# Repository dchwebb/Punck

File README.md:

# Punck

Overview
--------

- Audio Demo with Kick, snare and hi hats: [Punck.wav](https://raw.githubusercontent.com/dchwebb/Punck/master/Drum_Sequences/Punck.wav)
- Audio Demo with all voices and samples: [Punck2.wav](https://raw.githubusercontent.com/dchwebb/Punck/master/Drum_Sequences/Punck2.wav)

Punck is drum machine designed for use with Eurorack modular synthesizers. Its five primary voices are Kick, Snare, High Hat and two sample playback channels. In addition Toms and Claps voices are available via MIDI.

It features a built-in drum sequencer with five patterns each with up to 4 bars in length and either 16 or 24 beats per bar.

Voices can be triggered via front panel illuminated buttons, gate input, USB MIDI, serial MIDI and the drum sequencer. All trigger modes are available simultaneously.

Samples are stored on 32MB of internal Flash memory. This storage space is made available as a standard USB drive, requiring no external drives or SD cards.

A browser-based editor allows drum sequences to be entered graphically and detailed parameters of internal voices to be edited. A MIDI mapping facility provides access to different articulations of voices and different samples for the sampler tracks.

Audio DSP
---------

### Kick
The kick drum is modelled on a Roland TR-808 kick. This is generated in five phases, the first three providing an initial steep ramp and discontinuity for the 'click', a fast sine wave at 130Hz and then a slowly decelerating sine wave starting at 60Hz. A potentiometer-controlled 2-pole low pass filter softens the attack and a decay control adjusts the rate at which the level is reduced.

### Snare
The snare is formed of 3 pitched sine wave partials representing the body of the drum and a noise component representing the snare. The partials form the first three modes of vibration of the body. The initial frequency is potentiometer-controlled and the next two partials pitched at multiples of 1.588 and 1.833. The noise component is derived from two random number readings (left and right) and has a decay rate separate from the overall volume envelope. A potentiometer-controlled 2-pole low pass filter attenuates the high frequencies.

### Hi hat
The hi hat consists of 6 square waves with varying rates and levels of frequency modulation. In addition a stereo noise component is used at the beginning of the note. Separate 2-pole high and low pass filters use different ramp envelopes to increase the frequency of the HP filter and reduce the frequency of the LP filter as the note sustains. The decay of the noise and FM partials are separately configurable. When a range of MIDI notes is used to control the hi hat each note will result in a successively more 'open' hi hat sound.

### Sampler A and B
Two independent sample playback voices are provided. These play wave files (8, 16, 24 or 32 bit) stored in the internal flash storage. Each sampler can only play a single sample at a time allowing a maximum of two simultaneously playing voices. Each sampler has a speed control allowing a playback range of 0.5 - 1.5 original speed. Base playback speed is normalised to 48kHz from the original sample rate.

The sample's file name determines the bank (A or B) and index of the sample. Optionally adding suffix '.vNN' to the sample name will set the initial volume of the sample where NN is a value from 0 - 200% and 100% is the original sample level. Eg naming a sample 'B3crash.v150.wav' will make it the 3rd sample on bank B and will play at 150% of its original level.

### Toms
The Toms voice has no UI but is accessible from MIDI and the internal sequencer. An initial fast ramp is followed by a decelerating sine wave. Allocating multiple MIDI notes to playback will allow a range of pitches to be mapped over the MIDI notes.

### Claps
The Claps have no UI but are accessible from MIDI and the internal sequencer. Four 'claps' are played at slightly varying intervals with a sustained phase at the end of the fourth. Each clap is formed of band-pass filtered noise with a center frequency of 1250Hz and a Q of 3.

### Reverb
The reverb engine is derived from Geraint Luff's design: [Signalsmith Audio](https://signalsmith-audio.co.uk/writing/2021/lets-write-a-reverb/). This divides the stereo dry audio into 8 channels which then pass through various diffusion stages followed by a feedback mixer. The diffusion stages use short delay lines and a Hadamard mixing matrix to create a short diffused reverb. The feedback mixer uses longer delays to spread the diffusion channels. The 8 reverb channels are then mixed down to stereo and blended with the dry signal. A 2-pole Low pass filter is used at the input to control high end.

Architecture
------------

### Microcontroller

An STM32H743 microcontroller is responsible for voice generation, USB and MIDI handling, interfacing with the Flash storage devices via QSPI and true random number generation used to generate white noise for various voices. Code is written in C++ 20 using the STM32CubeIDE Eclipse-based IDE. All hardware interfacing is carried out through custom code (ie no STM HAL libraries).

Two internal ADCs read the various potentiometers using DMA circular mode. Timers in PWM mode are used to variably illuminate the LEDs integrated into the push buttons.

An external crystal clocked at 12MHz is scaled using the internal PLL to a main system clock of 400MHz. USB is clocked from the internal 48 MHz RC oscillator.

The microcontroller operates in device mode simultaneously managing three USB classes:

- Mass Storage Class:
Used to provide access to the internal sample flash memory so the storage can be accessed as a normal USB Flash drive. The storage is formatted using FAT16 file system.

- MIDI/Audio Class: 
Bi-directional MIDI is supported to enable playback of drum voices from a USB host. A sysex implementation allows the Browser editor to exchange configuration and playback information with the module.

- Communication Device Class:
A console application is provided to manage and debug the module. This provides information general maintenance tools, configuration options and tools for managing the internal flash storage (formatting, directory listings, disk analysis etc).

### Flash Storage
32MB of internal Flash memory is provided to allow internal sample storage. This consists of two 128Mbit Winbond W25Q128JVS chips connected via QSPI. The MCU operates the flash storage in Dual-flash mode, where 8 bits can be sent/received simultaneously by accessing two Flash memories in parallel. The memory is clocked at ~28MHz.

### Audio DAC
Punck uses a TI PCM5100APW Audio DAC clocked at 48kHz in stereo. The MCU interfaces with the DAC via I2S.

### Audio and Input Conditioning
The stereo audio signal is amplified with a gain of -2.74 using a TL074 op-amp. This also amplifies the tempo clock out signal to around a 5V level. Input clamping is done with MMBT3904 transistors.

### Power Supplies

The Eurorack +/-12V rails have reverse polarity protection and filtering and are then scaled to separate digital and analog 3.3V rails. The 3.3V MCU and DAC digital power supplies are provided by a TI TPS561201 switched-mode synchronous step-down power supply. An LD1117-3.3 linear regulator supplies the analog 3.3V power. A common digital/analog ground plane is used.

- +12V Current Draw: 123mA
- -12V Current Draw: 8mA

Construction
------------

The module is constructed using a sandwich of three PCBs. Schematic and PCB layout carried out in Kicad v6.08.

The component board is a four layer PCB with top mounted components, two inner ground layers and mainly power routing on the bottom layer. 

The control board is a two layer board on which are mounted the jacks, potentiometers, buttons and USB. 

The front panel is a two layer black PCB with exposed coated copper labels and marking.

The prototype was hand-soldered in sections to test each part of the hardware in isolation. This picture shows the power supplies (right), microcontroller (center) and two flash chips (above and to the left of the MCU). The audio DAC and op-amp will be placed on the left hand side:

Web Editor
----------

A Chrome-based web editor allows editing of the 5 internal drum sequences:

Each sequence can be up to 4 bars long with either 16 or 24 steps per bar. The level of each hit can be set and voice specific settings applied (eg choosing sample, snare sustain, hi-hat open/closed amount, tom pitch). Drum sequences can be exported and imported as json files.
Playback start/stop and sequence selection can be controlled from the editor.

Internal drum voice and reverb settings can also be edited:

Prototype
---------

Development was done on an STM Nucleo development board with external surface mount ICs (flash, DAC) soldered to breakout boards for prototyping:

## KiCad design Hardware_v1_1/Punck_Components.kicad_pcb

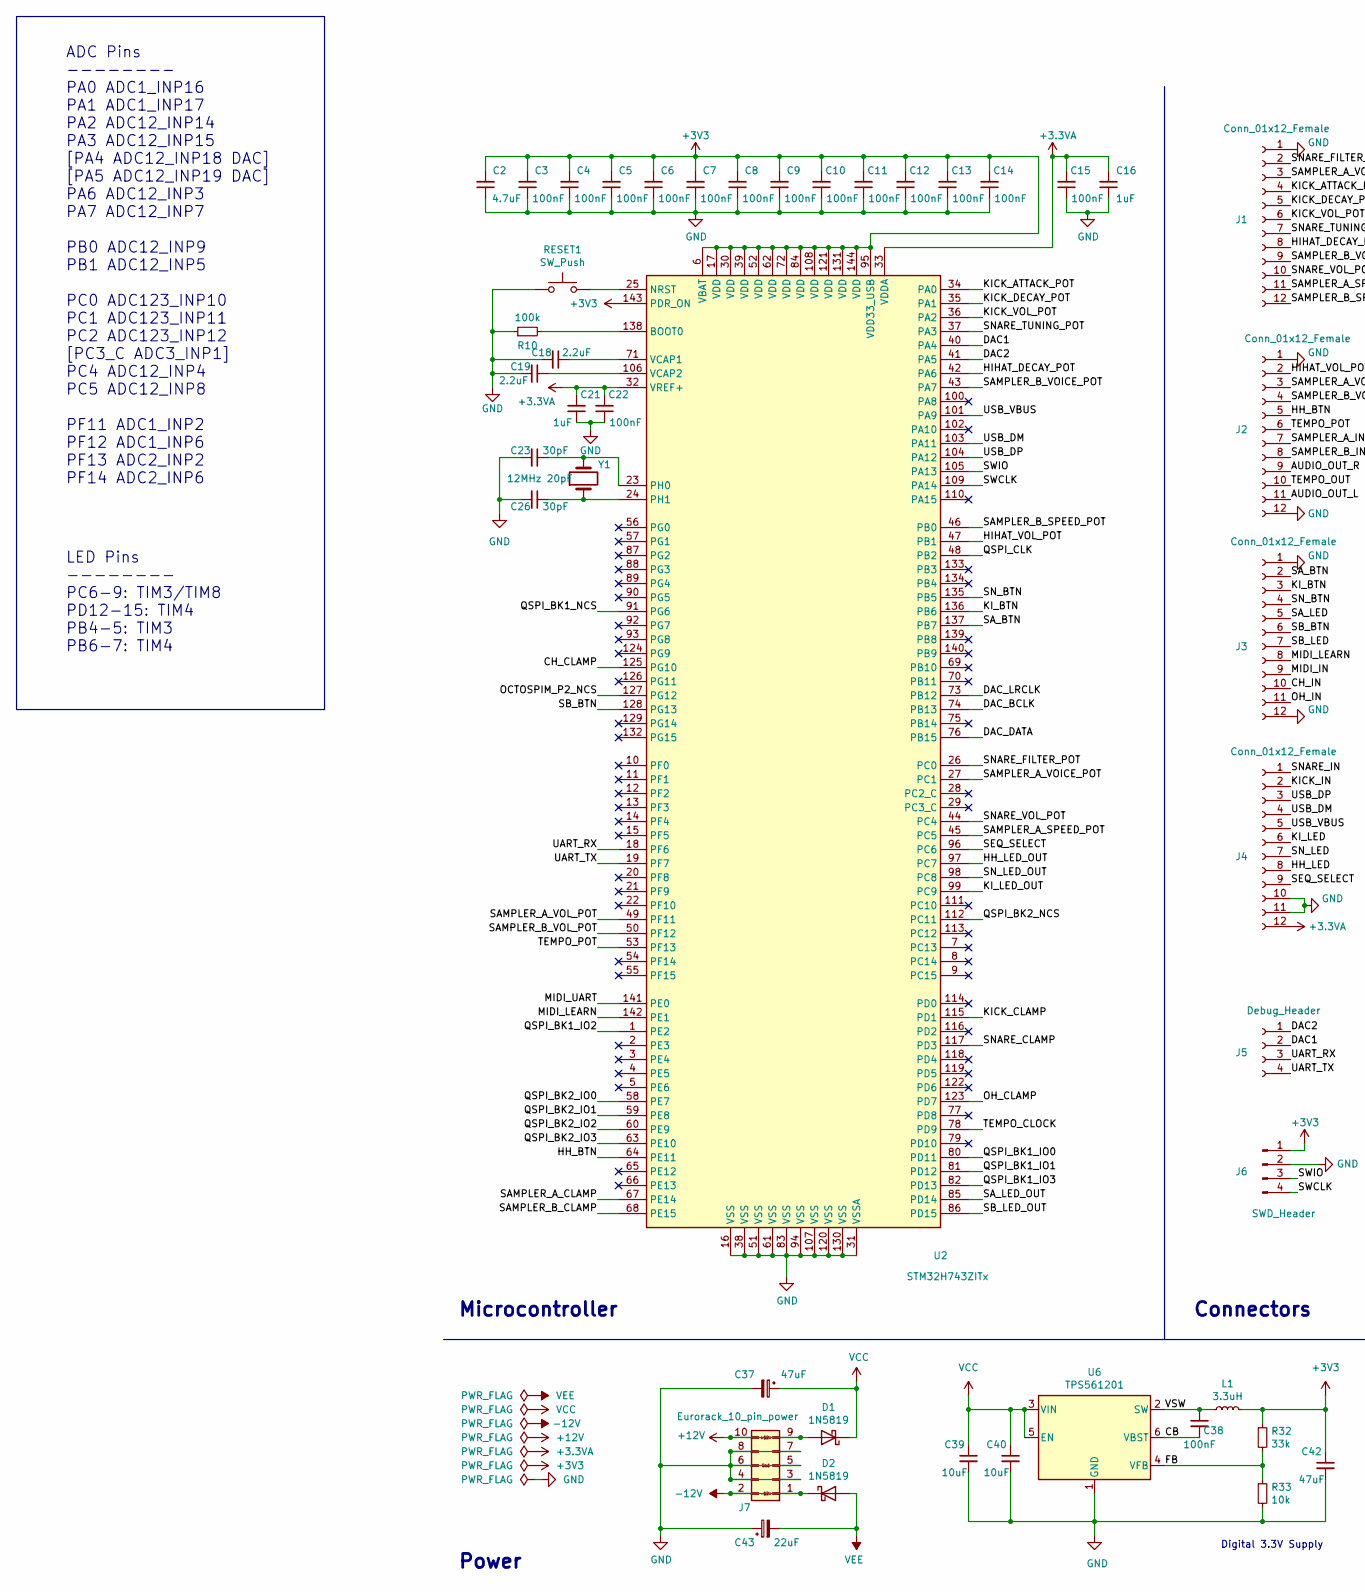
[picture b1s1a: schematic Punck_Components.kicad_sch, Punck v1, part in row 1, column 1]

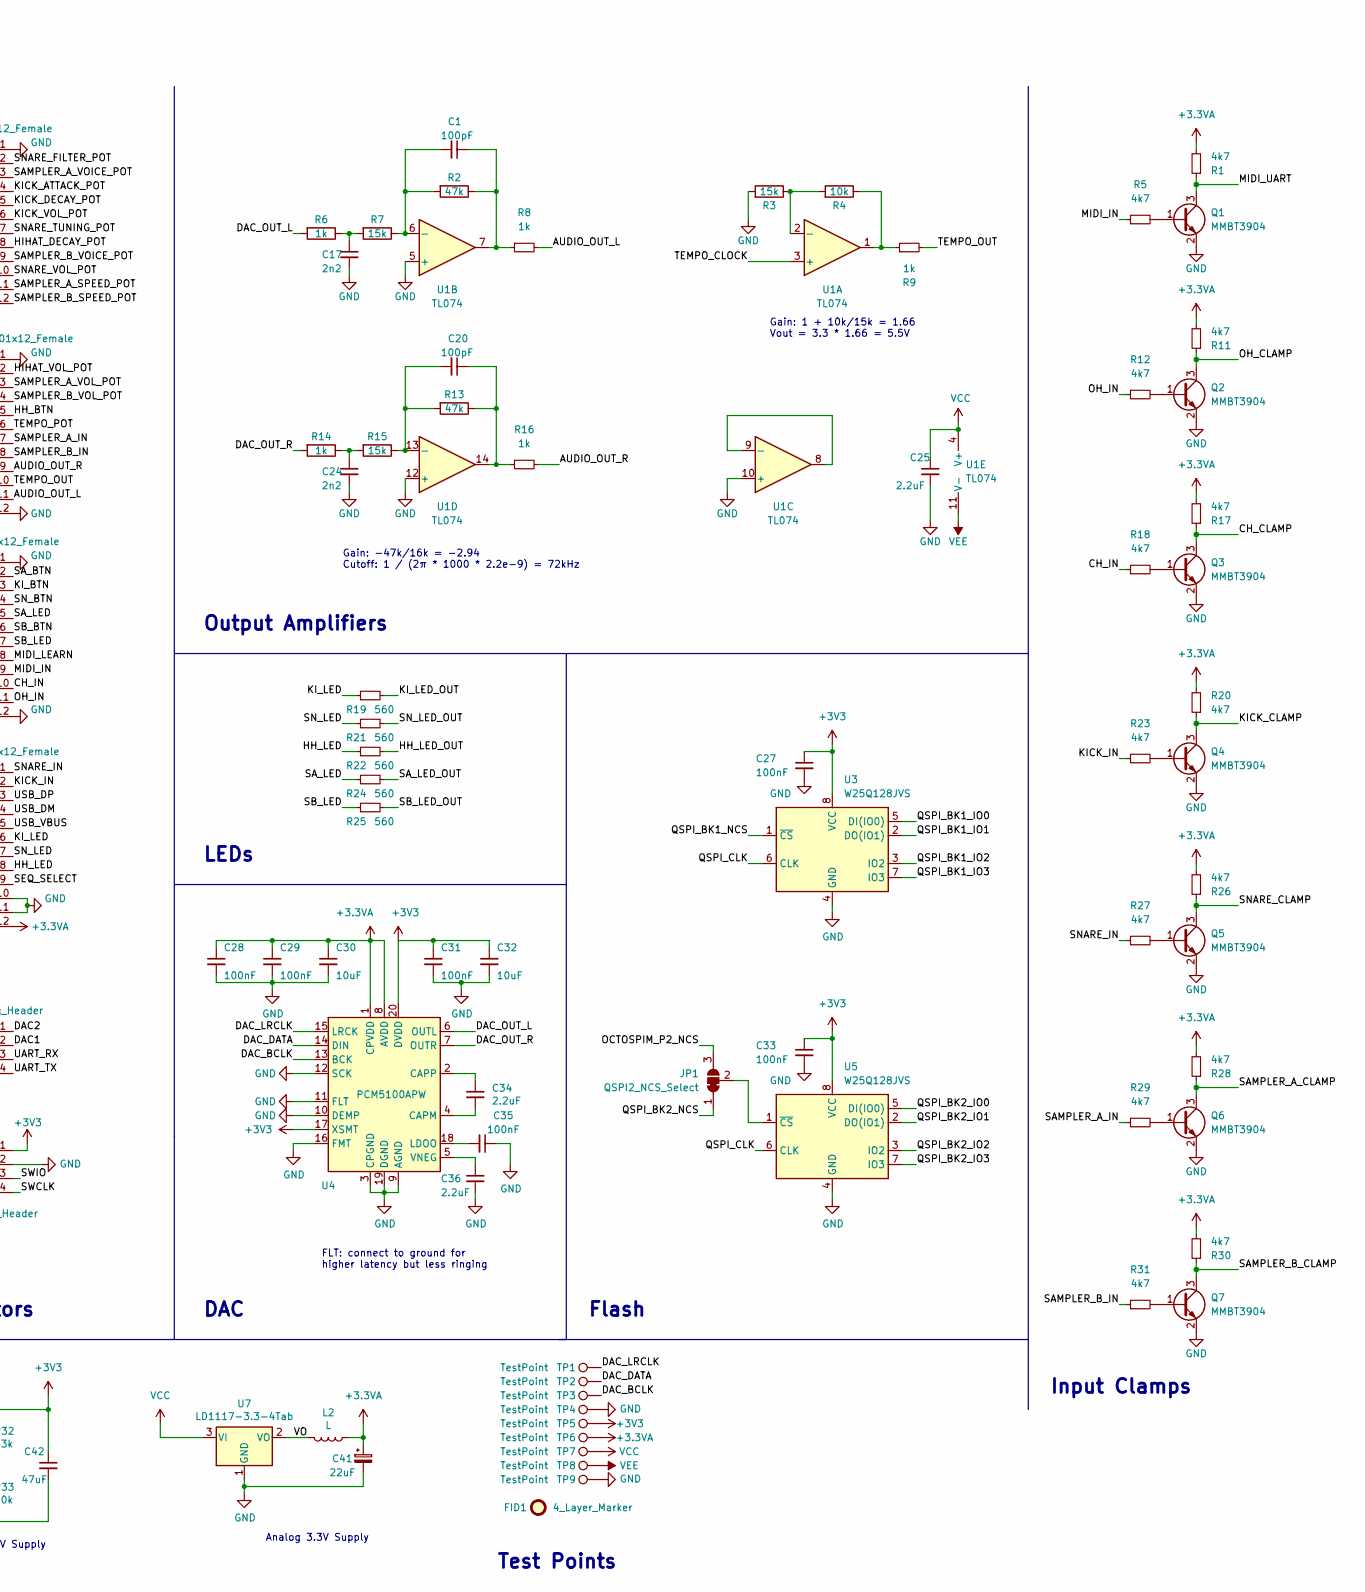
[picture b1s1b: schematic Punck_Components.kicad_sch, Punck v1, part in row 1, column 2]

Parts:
C1, C20: 100pF; C_0603_1608Metric_Pad1.08x0.95mm_HandSolder; Part_Number C14858
C2: 4.7uF; C_0603_1608Metric_Pad1.08x0.95mm_HandSolder; Part_Number C14663
C3, C4, C5, C6, C7, C8, C9, C10, C11, C12, C13, C14, C15, C22, C27, C28, C29, C31, C33, C35: 100nF; C_0603_1608Metric_Pad1.08x0.95mm_HandSolder; Part_Number C14663
C16, C21: 1uF; C_0603_1608Metric_Pad1.08x0.95mm_HandSolder; Part_Number C14663
C17, C24: 2n2; C_0603_1608Metric_Pad1.08x0.95mm_HandSolder; Part_Number C1588
C18, C19, C25, C34, C36: 2.2uF; C_0603_1608Metric_Pad1.08x0.95mm_HandSolder; Part_Number C23630
C23, C26: 30pF; C_0603_1608Metric_Pad1.08x0.95mm_HandSolder; Part_Number C22397
C30, C32: 10uF; C_0805_2012Metric; Part_Number C15850
C37: 47uF; CP_Elec_5x5.8; Part_Number C134798
C38: 100nF; C_0805_2012Metric; Part_Number C57112
C39, C40: 10uF; C_0805_2012Metric; Part_Number C57112
C41, C43: 22uF; CP_Elec_4x5.8; Part_Number C134793
C42: 47uF; R_1206_3216Metric; Part_Number C57112
D1, D2: 1N5819; D_SOD-123; Part_Number C8598
FID1: 4_Layer_Marker; 4_Layer_Markers
J1, J2, J3, J4: Conn_01x12_Female; PinHeader_1x12_P2.54mm_Vertical
J5: Debug_Header; PinHeader_1x04_P2.54mm_Vertical
J6: SWD_Header; SWD_header
J7: Eurorack_10_pin_power; Eurorack_10_pin_header
JP1: QSPI2_NCS_Select; SolderJumper-3_P1.3mm_Bridged12_RoundedPad1.0x1.5mm
L1: 3.3uH; L_0806; Part_Number C326343
L2: L; L_0805_2012Metric; Part_Number C1046
Q1, Q2, Q3, Q4, Q5, Q6, Q7: MMBT3904; SOT-23; Part_Number C20526
R1, R5, R11, R12, R17, R18, R20, R23, R26, R27, R28, R29, R30, R31: 4k7; R_0603_1608Metric_Pad0.98x0.95mm_HandSolder; Part_Number C23162
R2, R13: 47k; R_0603_1608Metric_Pad0.98x0.95mm_HandSolder; Part_Number C25819
R3, R7, R15: 15k; R_0603_1608Metric_Pad0.98x0.95mm_HandSolder; Part_Number C25804
R4: 10k; R_0603_1608Metric_Pad0.98x0.95mm_HandSolder; Part_Number C25819
R6, R14: 1k; R_0603_1608Metric_Pad0.98x0.95mm_HandSolder; Part_Number C4190
R8, R9, R16: 1k; R_0603_1608Metric_Pad0.98x0.95mm_HandSolder
R10: 100k; R_0603_1608Metric; Part_Number C25803
R19, R21, R22, R24, R25: 560; R_0603_1608Metric_Pad0.98x0.95mm_HandSolder; Part_Number C23162
R32: 33k; R_0603_1608Metric_Pad0.98x0.95mm_HandSolder
R33: 10k; R_0603_1608Metric_Pad0.98x0.95mm_HandSolder
RESET1: SW_Push; SW_SPST_EVQQ2
TP1, TP2, TP3, TP4, TP5, TP6, TP7, TP8, TP9: TestPoint; 1.3mm_Test_Point
U1: TL074; SOIC-14_3.9x8.7mm_P1.27mm
U2: STM32H743ZITx; LQFP-144_20x20mm_P0.5mm; Part_Number C114408
U3, U5: W25Q128JVS; SOIC-8_5.23x5.23mm_P1.27mm
U4: PCM5100APW; SSOP-20_4.4x6.5mm_Pitch0.65mm_Round_Pads; Part_Number C131154
U6: TPS561201; SOT-23-6_Handsoldering
U7: LD1117-3.3-4Tab; SOT-223-3_TabPin2
Y1: 12MHz 20pF; Crystal_SMD_5032-2Pin_5.0x3.2mm; Part_Number C115962

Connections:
+3.3VA: C15.2, C16.2, C21.2, C22.2, C28.1, C29.1, C30.1, C41.1, J4.12, L2.1, R1.2, R11.2, R17.2, R20.2, R26.2, R28.2, R30.2, TP6.1, U2.32 (VREF+), U2.33 (VDDA), U4.1 (CPVDD), U4.8 (AVDD)
+3V3: C2.2, C3.2, C4.2, C5.2, C6.2, C7.2, C8.2, C9.2, C10.2, C11.2, C12.2, C13.2, C14.2, C27.1, C31.1, C32.1, C33.1, C42.1, J6.1, L1.2, R32.1, TP5.1, U2.6 (VBAT), U2.17 (VDD), U2.30 (VDD), U2.39 (VDD), U2.52 (VDD), U2.62 (VDD), U2.72 (VDD), U2.84 (VDD), U2.95 (VDD33_USB), U2.108 (VDD), U2.121 (VDD), U2.131 (VDD), U2.143 (PDR_ON), U2.144 (VDD), U3.8 (VCC), U4.17 (XSMT), U4.20 (DVDD), U5.8 (VCC)
+12V: D1.2 (A), J7.9, J7.10
-12V: D2.1 (K), J7.1, J7.2
/AUDIO_OUT_L: J2.11, R8.2
/AUDIO_OUT_R: J2.9, R16.2
/CB: C38.2, U6.6 (VBST)
/CH_CLAMP: Q3.3 (C), R17.1, U2.125 (PG10)
/CH_IN: J3.10, R18.1
/DAC1: J5.2, U2.40 (PA4)
/DAC2: J5.1, U2.41 (PA5)
/DAC_BCLK: TP3.1, U2.74 (PB13), U4.13 (BCK)
/DAC_DATA: TP2.1, U2.76 (PB15), U4.14 (DIN)
/DAC_LRCLK: TP1.1, U2.73 (PB12), U4.15 (LRCK)
/DAC_OUT_L: R6.2, U4.6 (OUTL)
/DAC_OUT_R: R14.2, U4.7 (OUTR)
/FB: R32.2, R33.1, U6.4 (VFB)
/HH_BTN: J2.5, U2.64 (PE11)
/HH_LED: J4.8, R22.1
/HH_LED_OUT: R22.2, U2.97 (PC7)
/HIHAT_DECAY_POT: J1.8, U2.42 (PA6)
/HIHAT_VOL_POT: J2.2, U2.47 (PB1)
/KICK_ATTACK_POT: J1.4, U2.34 (PA0)
/KICK_CLAMP: Q4.3 (C), R20.1, U2.115 (PD1)
/KICK_DECAY_POT: J1.5, U2.35 (PA1)
/KICK_IN: J4.2, R23.1
/KICK_VOL_POT: J1.6, U2.36 (PA2)
/KI_BTN: J3.3, U2.136 (PB6)
/KI_LED: J4.6, R19.1
/KI_LED_OUT: R19.2, U2.99 (PC9)
/MIDI_IN: J3.9, R5.1
/MIDI_LEARN: J3.8, U2.142 (PE1)
/MIDI_UART: Q1.3 (C), R1.1, U2.141 (PE0)
/OCTOSPIM_P2_NCS: JP1.3 (B), U2.127 (PG12)
/OH_CLAMP: Q2.3 (C), R11.1, U2.123 (PD7)
/OH_IN: J3.11, R12.1
/QSPI_BK1_IO0: U2.80 (PD11), U3.5 (DI(IO0))
/QSPI_BK1_IO1: U2.81 (PD12), U3.2 (DO(IO1))
/QSPI_BK1_IO2: U2.1 (PE2), U3.3 (IO2)
/QSPI_BK1_IO3: U2.82 (PD13), U3.7 (IO3)
/QSPI_BK1_NCS: U2.91 (PG6), U3.1 (~CS)
/QSPI_BK2_IO0: U2.58 (PE7), U5.5 (DI(IO0))
/QSPI_BK2_IO1: U2.59 (PE8), U5.2 (DO(IO1))
/QSPI_BK2_IO2: U2.60 (PE9), U5.3 (IO2)
/QSPI_BK2_IO3: U2.63 (PE10), U5.7 (IO3)
/QSPI_BK2_NCS: JP1.1 (A), U2.112 (PC11)
/QSPI_CLK: U2.48 (PB2), U3.6 (CLK), U5.6 (CLK)
/SAMPLER_A_CLAMP: Q6.3 (C), R28.1, U2.67 (PE14)
/SAMPLER_A_IN: J2.7, R29.1
/SAMPLER_A_SPEED_POT: J1.11, U2.45 (PC5)
/SAMPLER_A_VOICE_POT: J1.3, U2.27 (PC1)
/SAMPLER_A_VOL_POT: J2.3, U2.49 (PF11)
/SAMPLER_B_CLAMP: Q7.3 (C), R30.1, U2.68 (PE15)
/SAMPLER_B_IN: J2.8, R31.1
/SAMPLER_B_SPEED_POT: J1.12, U2.46 (PB0)
/SAMPLER_B_VOICE_POT: J1.9, U2.43 (PA7)
/SAMPLER_B_VOL_POT: J2.4, U2.50 (PF12)
/SA_BTN: J3.2, U2.137 (PB7)
/SA_LED: J3.5, R24.1
/SA_LED_OUT: R24.2, U2.85 (PD14)
/SB_BTN: J3.6, U2.128 (PG13)
/SB_LED: J3.7, R25.1
/SB_LED_OUT: R25.2, U2.86 (PD15)
/SEQ_SELECT: J4.9, U2.96 (PC6)
/SNARE_CLAMP: Q5.3 (C), R26.1, U2.117 (PD3)
/SNARE_FILTER_POT: J1.2, U2.26 (PC0)
/SNARE_IN: J4.1, R27.1
/SNARE_TUNING_POT: J1.7, U2.37 (PA3)
/SNARE_VOL_POT: J1.10, U2.44 (PC4)
/SN_BTN: J3.4, U2.135 (PB5)
/SN_LED: J4.7, R21.1
/SN_LED_OUT: R21.2, U2.98 (PC8)
/SWCLK: J6.4, U2.109 (PA14)
/SWIO: J6.3, U2.105 (PA13)
/TEMPO_CLOCK: U1.3 (+), U2.78 (PD9)
/TEMPO_OUT: J2.10, R9.2
/TEMPO_POT: J2.6, U2.53 (PF13)
/UART_RX: J5.3, U2.18 (PF6)
/UART_TX: J5.4, U2.19 (PF7)
/USB_DM: J4.4, U2.103 (PA11)
/USB_DP: J4.3, U2.104 (PA12)
/USB_VBUS: J4.5, U2.101 (PA9)
/VO: L2.2, U7.2 (VO)
/VSW: C38.1, L1.1, U6.2 (SW)
GND: C2.1, C3.1, C4.1, C5.1, C6.1, C7.1, C8.1, C9.1, C10.1, C11.1, C12.1, C13.1, C14.1, C15.1, C16.1, C17.2, C18.2, C19.2, C21.1, C22.1, C23.2, C24.2, C25.2, C26.2, C27.2, C28.2, C29.2, C30.2, C31.2, C32.2, C33.2, C35.1, C36.2, C37.2, C39.2, C40.2, C41.2, C42.2, C43.1, J1.1, J2.1, J2.12, J3.1, J3.12, J4.10, J4.11, J6.2, J7.3, J7.4, J7.5, J7.6, J7.7, J7.8, Q1.2 (E), Q2.2 (E), Q3.2 (E), Q4.2 (E), Q5.2 (E), Q6.2 (E), Q7.2 (E), R3.2, R10.1, R33.2, RESET1.2, TP4.1, TP9.1, U1.5 (+), U1.10 (+), U1.12 (+), U2.16 (VSS), U2.31 (VSSA), U2.38 (VSS), U2.51 (VSS), U2.61 (VSS), U2.83 (VSS), U2.94 (VSS), U2.107 (VSS), U2.120 (VSS), U2.130 (VSS), U3.4 (GND), U4.3 (CPGND), U4.9 (AGND), U4.10 (DEMP), U4.11 (FLT), U4.12 (SCK), U4.16 (FMT), U4.19 (DGND), U5.4 (GND), U6.1 (GND), U7.1 (GND)
unnamed: C1.1, R2.1, R8.1, U1.7
unnamed: C1.2, R2.2, R7.1, U1.6 (-)
unnamed: C17.1, R6.1, R7.2
unnamed: C18.1, U2.71 (VCAP1)
unnamed: C19.1, U2.106 (VCAP2)
unnamed: C20.1, R13.1, R16.1, U1.14
unnamed: C20.2, R13.2, R15.1, U1.13 (-)
unnamed: C23.1, U2.23 (PH0), Y1.2
unnamed: C24.1, R14.1, R15.2
unnamed: C26.1, U2.24 (PH1), Y1.1
unnamed: C34.1, U4.2 (CAPP)
unnamed: C34.2, U4.4 (CAPM)
unnamed: C35.2, U4.18 (LDOO)
unnamed: C36.1, U4.5 (VNEG)
unnamed: JP1.2 (C), U5.1 (~CS)
unnamed: Q1.1 (B), R5.2
unnamed: Q2.1 (B), R12.2
unnamed: Q3.1 (B), R18.2
unnamed: Q4.1 (B), R23.2
unnamed: Q5.1 (B), R27.2
unnamed: Q6.1 (B), R29.2
unnamed: Q7.1 (B), R31.2
unnamed: R3.1, R4.2, U1.2 (-)
unnamed: R4.1, R9.1, U1.1
unnamed: R10.2, U2.138 (BOOT0)
unnamed: RESET1.1, U2.25 (NRST)
unnamed: U1.8, U1.9 (-)
VCC: C25.1, C37.1, C39.1, C40.1, D1.1 (K), TP7.1, U1.4 (V+), U6.3 (VIN), U6.5 (EN), U7.3 (VI)
VEE: C43.2, D2.2 (A), TP8.1, U1.11 (V-)

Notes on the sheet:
Digital 3.3V Supply
Gain: 1 + 10k/15k = 1.66 Vout = 3.3 * 1.66 = 5.5V
ADC Pins -------- PA0 ADC1_INP16 PA1 ADC1_INP17 PA2 ADC12_INP14 PA3 ADC12_INP15 [PA4 ADC12_INP18 DAC] [PA5 ADC12_INP19 DAC] PA6 ADC12_INP3 PA7 ADC12_INP7 PB0 ADC12_INP9 PB1 ADC12_INP5 PC0 ADC123_INP10 PC1 ADC123_INP11 PC2 ADC123_INP12 [PC3_C ADC3_INP1] PC4 ADC12_INP4 PC5 ADC12_INP8 PF11 ADC1_INP2 P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
Gain: -47k/16k = -2.94 Cutoff: 1 / (2π * 1000 * 2.2e-9) = 72kHz
Microcontroller
Connectors
Analog 3.3V Supply
LED Pins -------- PC6-9: TIM3/TIM8 PD12-15: TIM4 PB4-5: TIM3 PB6-7: TIM4
LEDs
Power
Flash
DAC
Output Amplifiers
FLT: connect to ground for higher latency but less ringing
Test Points
Input Clamps

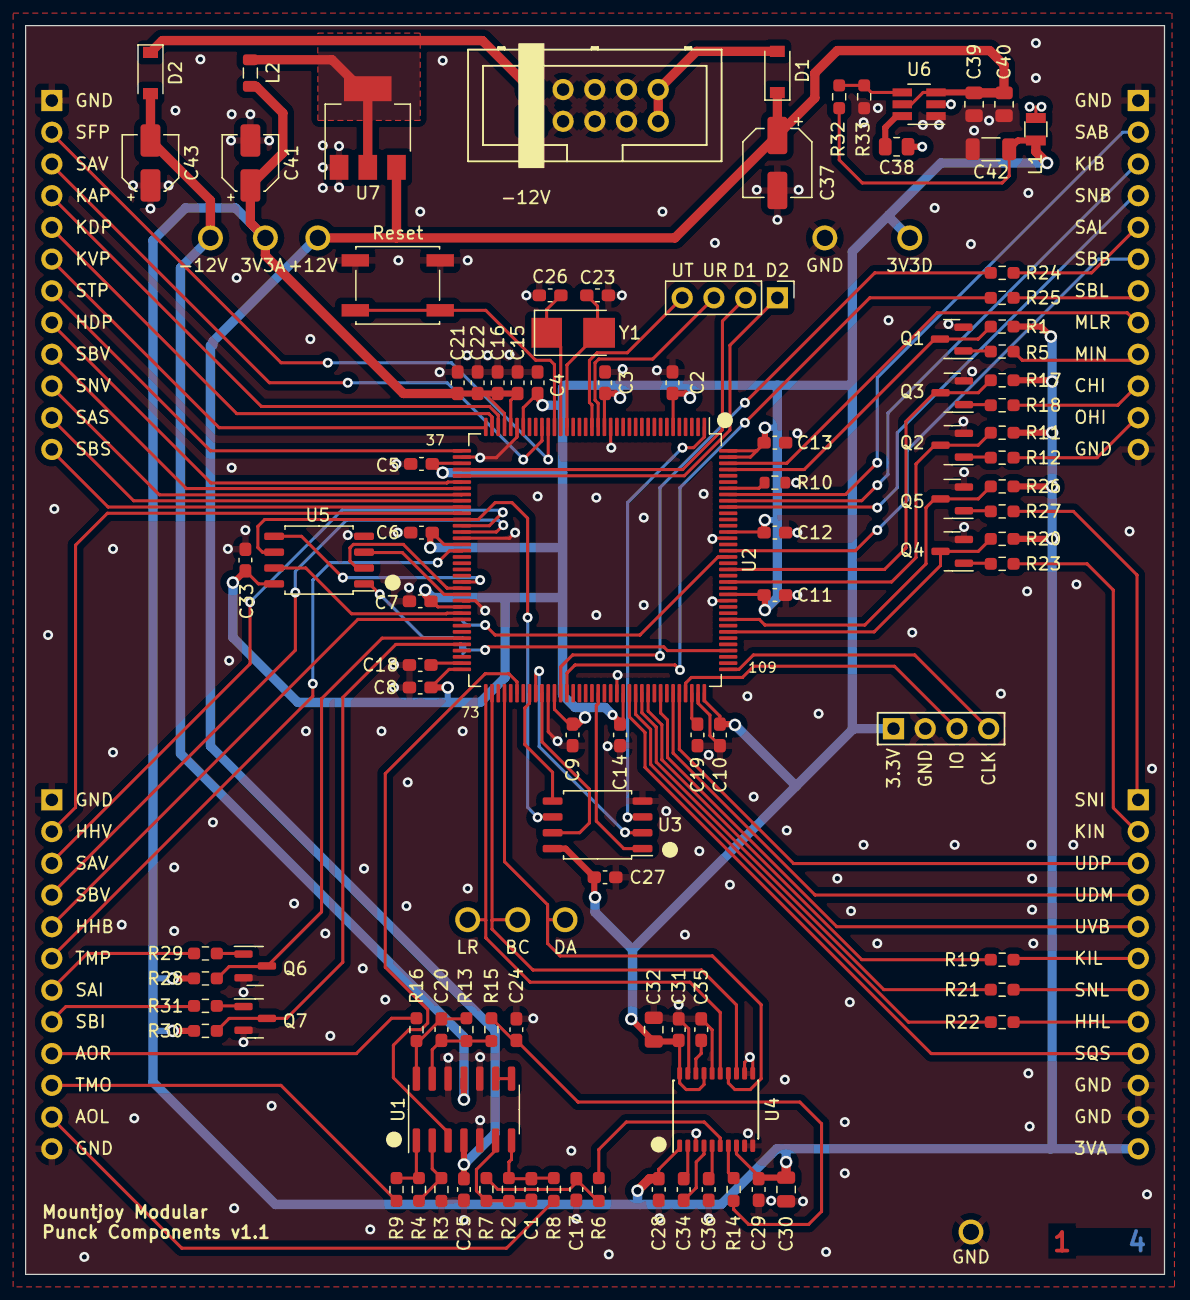
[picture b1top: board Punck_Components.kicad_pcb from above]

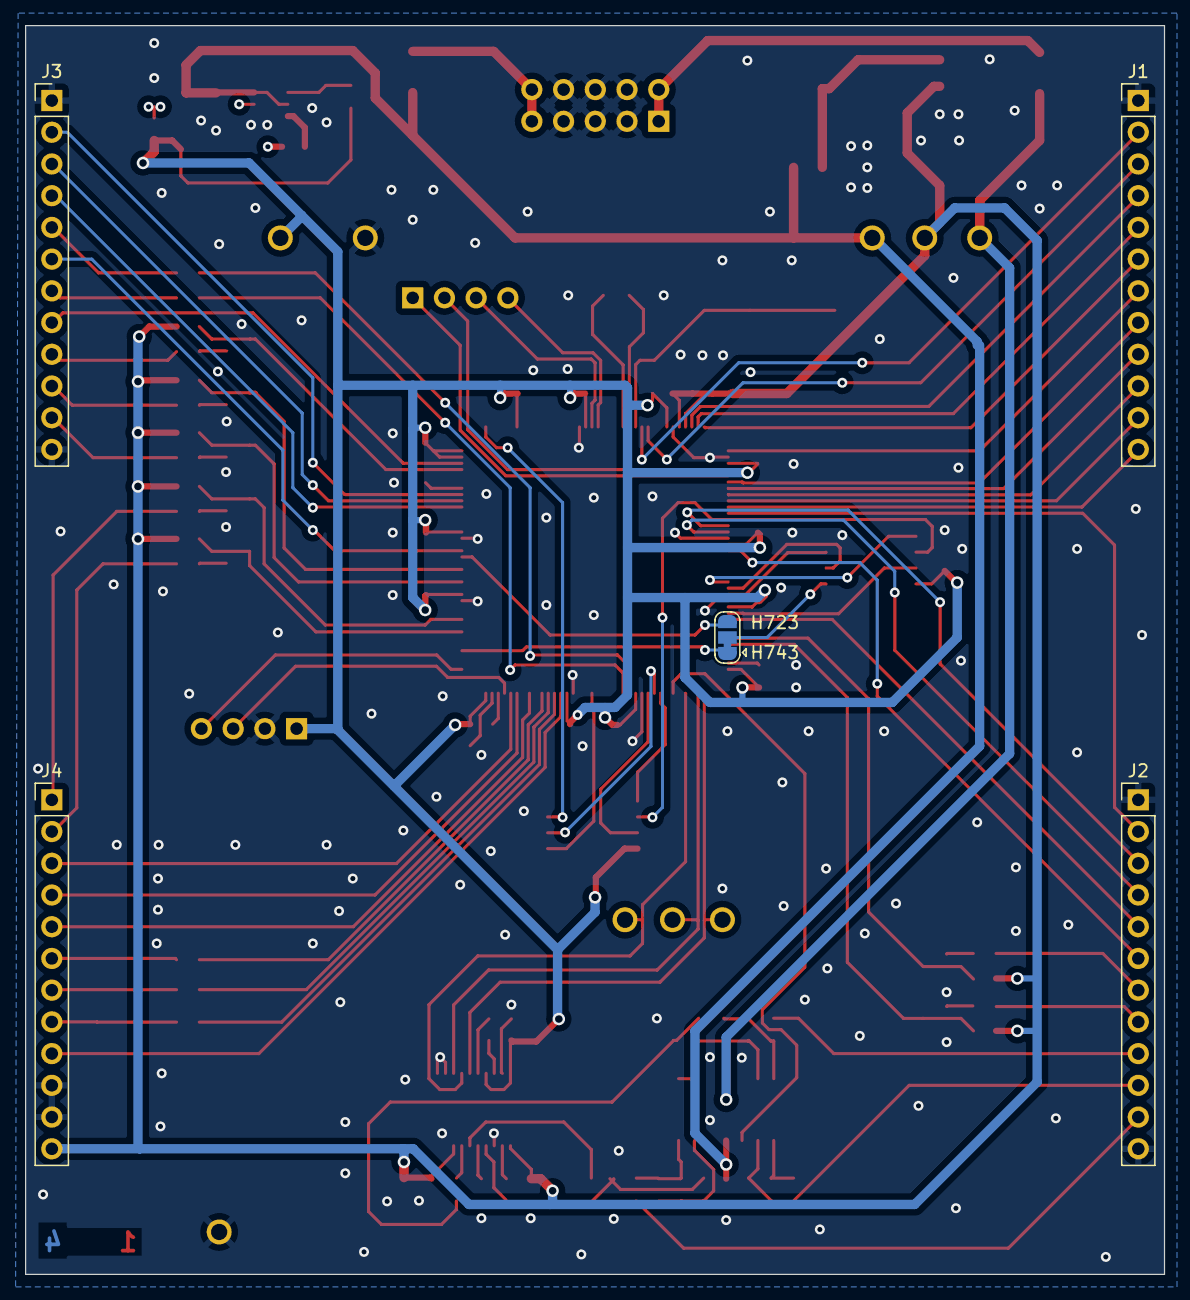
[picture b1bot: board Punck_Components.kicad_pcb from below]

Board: 4 copper layers, 91.2 x 100.0 mm, 114 parts (5 on the bottom side), 114 nets.

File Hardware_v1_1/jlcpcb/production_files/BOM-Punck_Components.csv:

Comment,Designator,Footprint,LCSC
L,L2,L_0805_2012Metric,C1015
STM32H743ZITx,U2,LQFP-144_20x20mm_P0.5mm,C114408
PCM5100APW,U4,SSOP-20_4.4x6.5mm_Pitch0.65mm_Round_Pads,C131154
TPS561201,U6,SOT-23-6_Handsoldering,C133965
100nF,"C10,C11,C12,C13,C14,C15,C22,C27,C28,C29,C3,C31,C33,C35,C4,C5,C6,C7,C8,C9",C_0603_1608Metric_Pad1.08x0.95mm_HandSolder,C14663
100pF,"C1,C20",C_0603_1608Metric_Pad1.08x0.95mm_HandSolder,C14858
1uF,"C16,C21",C_0603_1608Metric_Pad1.08x0.95mm_HandSolder,C15849
2n2,"C17,C24",C_0603_1608Metric_Pad1.08x0.95mm_HandSolder,C1604
30pF,"C23,C26",C_0603_1608Metric_Pad1.08x0.95mm_HandSolder,C1658
47uF,"C37,C41,C43",CP_Elec_5x5.8,C178597
4.7uF,C2,C_0603_1608Metric_Pad1.08x0.95mm_HandSolder,C19666
MMBT3904,"Q1,Q2,Q3,Q4,Q5,Q6,Q7",SOT-23,C20526
1k,"R14,R16,R6,R8,R9",R_0603_1608Metric_Pad0.98x0.95mm_HandSolder,C21190
15k,"R15,R3,R7",R_0603_1608Metric_Pad0.98x0.95mm_HandSolder,C22809
4k7,"R1,R11,R12,R17,R18,R20,R23,R26,R27,R28,R29,R30,R31,R5",R_0603_1608Metric_Pad0.98x0.95mm_HandSolder,C23162
560,"R19,R21,R22,R24,R25",R_0603_1608Metric_Pad0.98x0.95mm_HandSolder,C23204
2.2uF,"C18,C19,C25,C34,C36",C_0603_1608Metric_Pad1.08x0.95mm_HandSolder,C23630
100k,R10,R_0603_1608Metric,C25803
10k,"R33,R4",R_0603_1608Metric_Pad0.98x0.95mm_HandSolder,C25804
47k,"R13,R2",R_0603_1608Metric_Pad0.98x0.95mm_HandSolder,C25819
100nF,C38,R_0805_2012Metric,C28233
33k,R32,R_0603_1608Metric_Pad0.98x0.95mm_HandSolder,C4216
10uF,"C30,C32,C39,C40",C_0805_2012Metric,C440198
12MHz 20pF,Y1,Crystal_SMD_5032-2Pin_5.0x3.2mm,C479171
LD1117-3.3-4Tab,U7,SOT-223-3_TabPin2,C6186
TL074,U1,SOIC-14_3.9x8.7mm_P1.27mm,C6963
1N5819,"D1,D2",D_SOD-123,C8598
47uF,C42,R_1206_3216Metric,C96123
W25Q128JVS,"U3,U5",SOIC-8_5.23x5.23mm_P1.27mm,C97521
3.3uH,L1,L_0806,C98336

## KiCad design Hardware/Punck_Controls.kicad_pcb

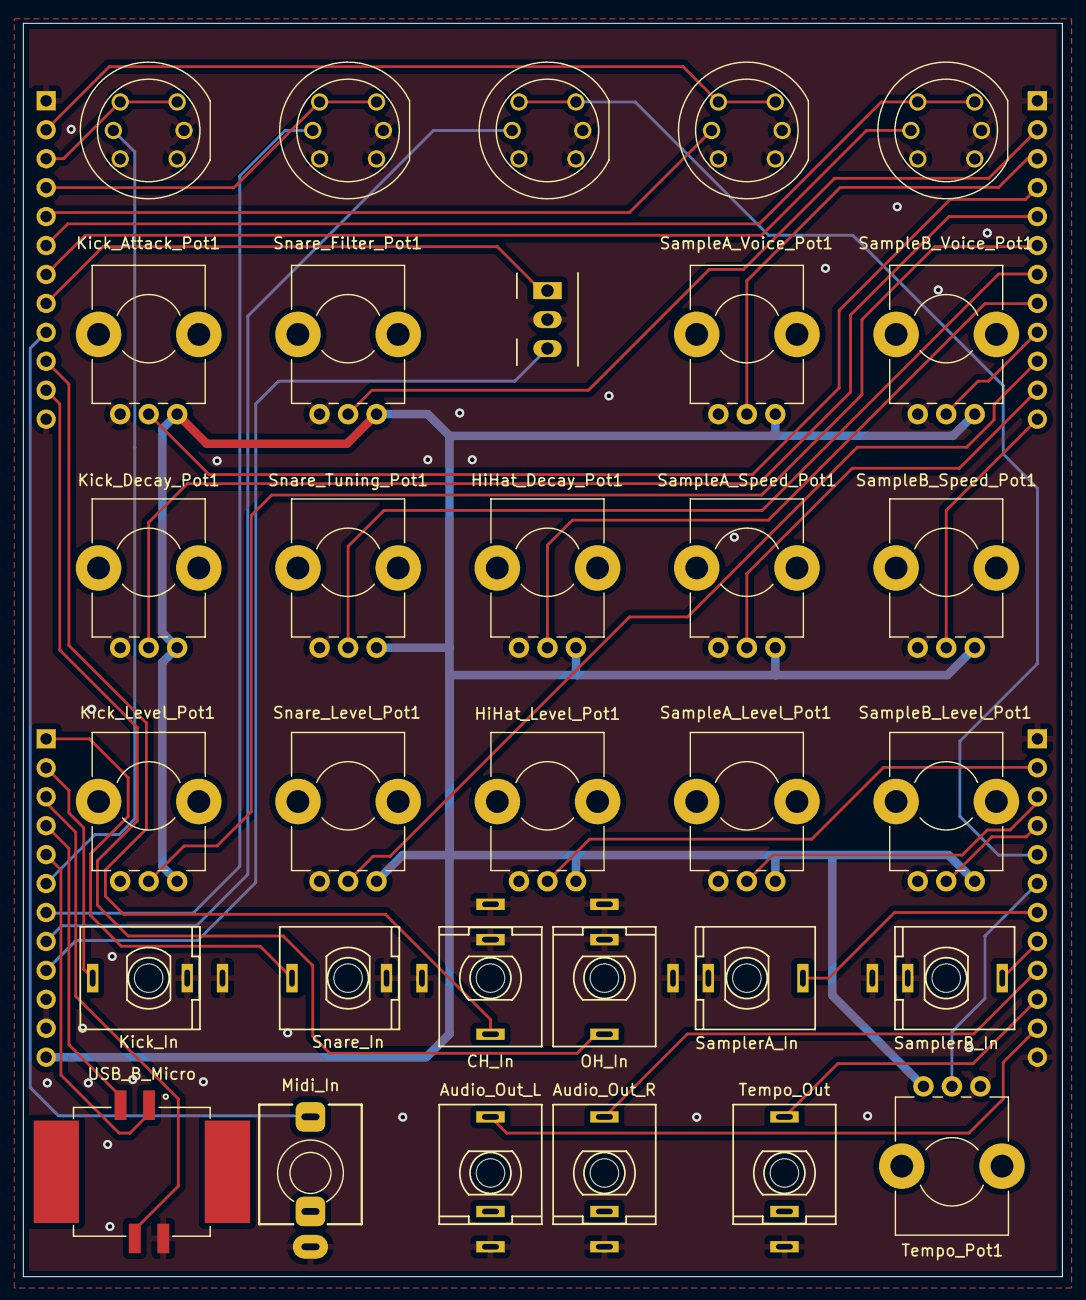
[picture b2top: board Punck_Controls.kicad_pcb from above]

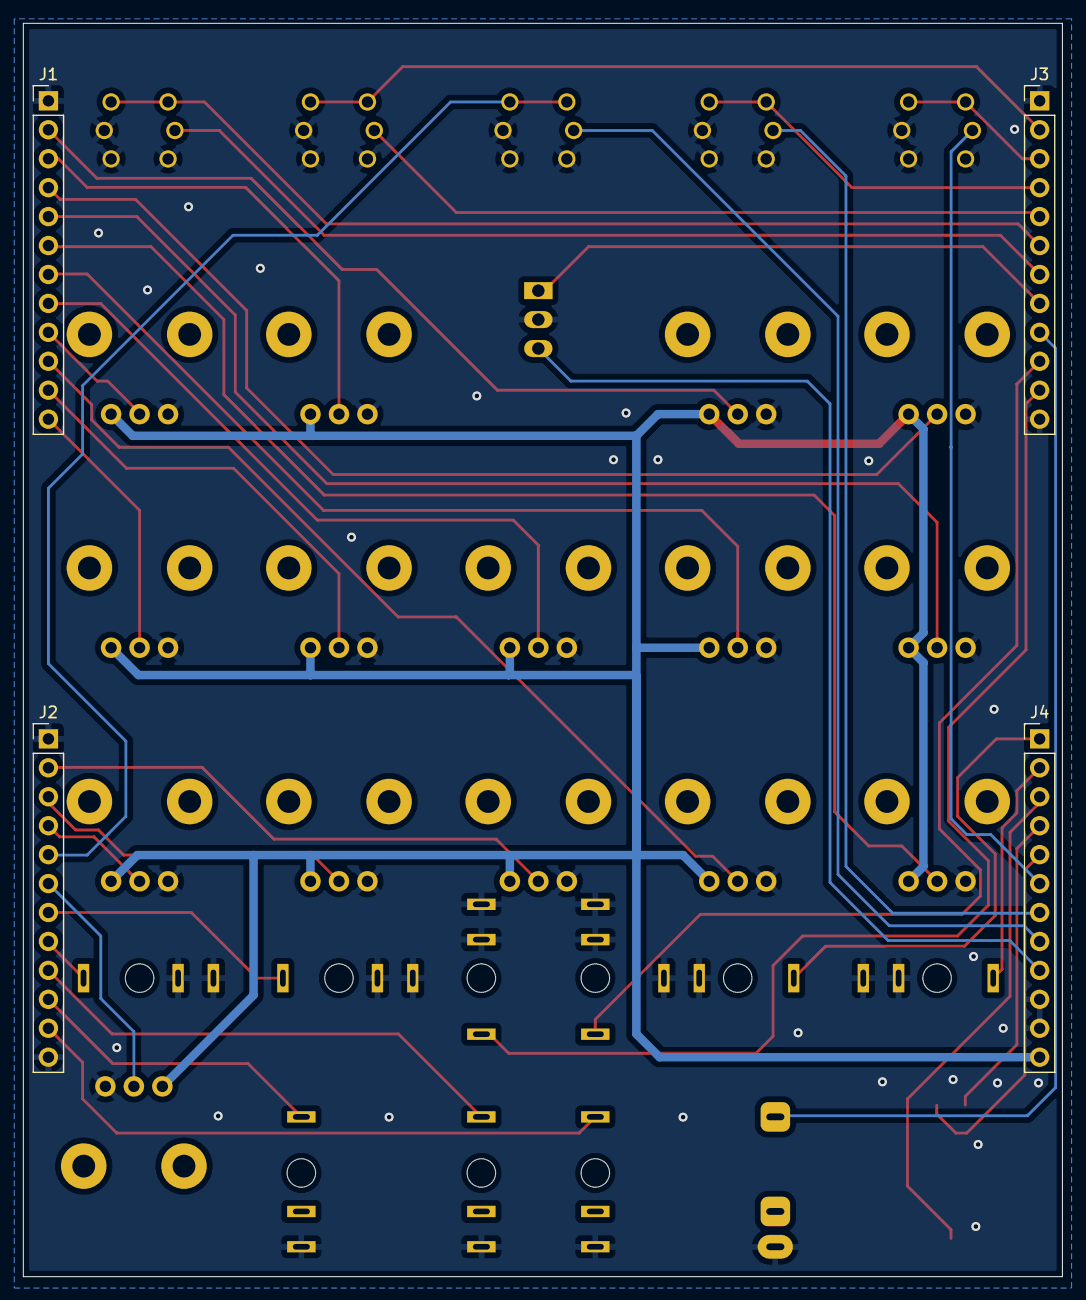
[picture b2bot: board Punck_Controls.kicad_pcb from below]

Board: 2 copper layers, 91.2 x 110.0 mm, 36 parts (4 on the bottom side), 42 nets.

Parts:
BTN1, BTN2, BTN3, BTN4, BTN5: KS01-BLV
BTN_MODE1: SW_SPDT_MSM; SPDT_SubMiniature_Aligned
HiHat_Decay_Pot1: B10k; Alpha_9mm_Potentiometer_Aligned
HiHat_Level_Pot1: B10k; Alpha_9mm_Potentiometer_Aligned
J1, J2, J3, J4: Conn_01x12_Female; PinHeader_1x12_P2.54mm_Vertical
J5: Snare_In; THONKICONN_hole
J6: CH_In; THONKICONN_hole
J7: OH_In; THONKICONN_hole
J8: SamplerA_In; THONKICONN_hole
J9: SamplerB_In; THONKICONN_hole
J10: Kick_In; THONKICONN_hole
J11: USB_B_Micro; USB_TE_1734517-1
J12: Tempo_Out; THONKICONN_hole
J13: Audio_Out_L; THONKICONN_hole
J14: Audio_Out_R; THONKICONN_hole
J15: Midi_In; Thonkiconn_Stereo-PJ366ST
Kick_Attack_Pot1: B10k; Alpha_9mm_Potentiometer_Aligned
Kick_Decay_Pot1: B10k; Alpha_9mm_Potentiometer_Aligned
Kick_Level_Pot1: B10k; Alpha_9mm_Potentiometer_Aligned
SampleA_Level_Pot1: B10k; Alpha_9mm_Potentiometer_Aligned
SampleA_Speed_Pot1: B10k; Alpha_9mm_Potentiometer_Aligned
SampleA_Voice_Pot1: B10k; Alpha_9mm_Potentiometer_Aligned
SampleB_Level_Pot1: B10k; Alpha_9mm_Potentiometer_Aligned
SampleB_Speed_Pot1: B10k; Alpha_9mm_Potentiometer_Aligned
SampleB_Voice_Pot1: B10k; Alpha_9mm_Potentiometer_Aligned
Snare_Filter_Pot1: B10k; Alpha_9mm_Potentiometer_Aligned
Snare_Level_Pot1: B10k; Alpha_9mm_Potentiometer_Aligned
Snare_Tuning_Pot1: B10k; Alpha_9mm_Potentiometer_Aligned
Tempo_Pot1: B10k; Alpha_9mm_Potentiometer_Aligned

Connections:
+3.3VA: HiHat_Decay_Pot1.1, HiHat_Level_Pot1.1, J4.12, Kick_Attack_Pot1.1, Kick_Decay_Pot1.1, Kick_Level_Pot1.1, SampleA_Level_Pot1.1, SampleA_Speed_Pot1.1, SampleA_Voice_Pot1.1, SampleB_Level_Pot1.1, SampleB_Speed_Pot1.1, SampleB_Voice_Pot1.1, Snare_Filter_Pot1.1, Snare_Level_Pot1.1, Snare_Tuning_Pot1.1, Tempo_Pot1.1
/AUDIO_OUT_L: J2.11, J13.3
/AUDIO_OUT_R: J2.9, J14.3
/CH_IN: J3.10, J6.3
/HH_BTN: BTN3.1, BTN3.2, J2.5
/HH_LED: BTN3.5 (A), J4.8
/HIHAT_DECAY_POT: HiHat_Decay_Pot1.2, J1.8
/HIHAT_VOL_POT: HiHat_Level_Pot1.2, J2.2
/KICK_ATTACK_POT: J1.4, Kick_Attack_Pot1.2
/KICK_DECAY_POT: J1.5, Kick_Decay_Pot1.2
/KICK_IN: J4.2, J10.3
/KICK_VOL_POT: J1.6, Kick_Level_Pot1.2
/KI_BTN: BTN1.1, BTN1.2, J3.3
/KI_LED: BTN1.5 (A), J4.6
/MIDI_IN: J3.9, J15.T
/MIDI_LEARN: BTN_MODE1.1, J3.8
/OH_IN: J3.11, J7.3
/SAMPLER_A_IN: J2.7, J8.3
/SAMPLER_A_SPEED_POT: J1.11, SampleA_Speed_Pot1.2
/SAMPLER_A_VOICE_POT: J1.3, SampleA_Voice_Pot1.2
/SAMPLER_A_VOL_POT: J2.3, SampleA_Level_Pot1.2
/SAMPLER_B_IN: J2.8, J9.3
/SAMPLER_B_SPEED_POT: J1.12, SampleB_Speed_Pot1.2
/SAMPLER_B_VOICE_POT: J1.9, SampleB_Voice_Pot1.2
/SAMPLER_B_VOL_POT: J2.4, SampleB_Level_Pot1.2
/SA_BTN: BTN4.1, BTN4.2, J3.2
/SA_LED: BTN4.5 (A), J3.5
/SB_BTN: BTN5.1, BTN5.2, J3.6
/SB_LED: BTN5.5 (A), J3.7
/SEQ_SELECT: BTN_MODE1.3, J4.9
/SNARE_FILTER_POT: J1.2, Snare_Filter_Pot1.2
/SNARE_IN: J4.1, J5.3
/SNARE_TUNING_POT: J1.7, Snare_Tuning_Pot1.2
/SNARE_VOL_POT: J1.10, Snare_Level_Pot1.2
/SN_BTN: BTN2.1, BTN2.2, J3.4
/SN_LED: BTN2.5 (A), J4.7
/TEMPO_OUT: J2.10, J12.3
/TEMPO_POT: J2.6, Tempo_Pot1.2
/USB_DM: J4.4, J11.2 (D-)
/USB_DP: J4.3, J11.3 (D+)
/USB_VBUS: J4.5, J11.1 (VCC)
GND: BTN1.3, BTN1.4, BTN1.6 (K), BTN2.3, BTN2.4, BTN2.6 (K), BTN3.3, BTN3.4, BTN3.6 (K), BTN4.3, BTN4.4, BTN4.6 (K), BTN5.3, BTN5.4, BTN5.6 (K), BTN_MODE1.2, HiHat_Decay_Pot1.3, HiHat_Level_Pot1.3, J1.1, J2.1, J2.12, J3.1, J3.12, J4.10, J4.11, J5.1, J5.2, J6.1, J6.2, J7.1, J7.2, J8.1, J8.2, J9.1, J9.2, J10.1, J10.2, J11.4 (GND), J12.1, J13.1, J14.1, J15.S, Kick_Attack_Pot1.3, Kick_Decay_Pot1.3, Kick_Level_Pot1.3, SampleA_Level_Pot1.3, SampleA_Speed_Pot1.3, SampleA_Voice_Pot1.3, SampleB_Level_Pot1.3, SampleB_Speed_Pot1.3, SampleB_Voice_Pot1.3, Snare_Filter_Pot1.3, Snare_Level_Pot1.3, Snare_Tuning_Pot1.3, Tempo_Pot1.3
